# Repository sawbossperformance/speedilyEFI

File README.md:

# speedilyEFI
Arduino based projects for the Automotive Industry

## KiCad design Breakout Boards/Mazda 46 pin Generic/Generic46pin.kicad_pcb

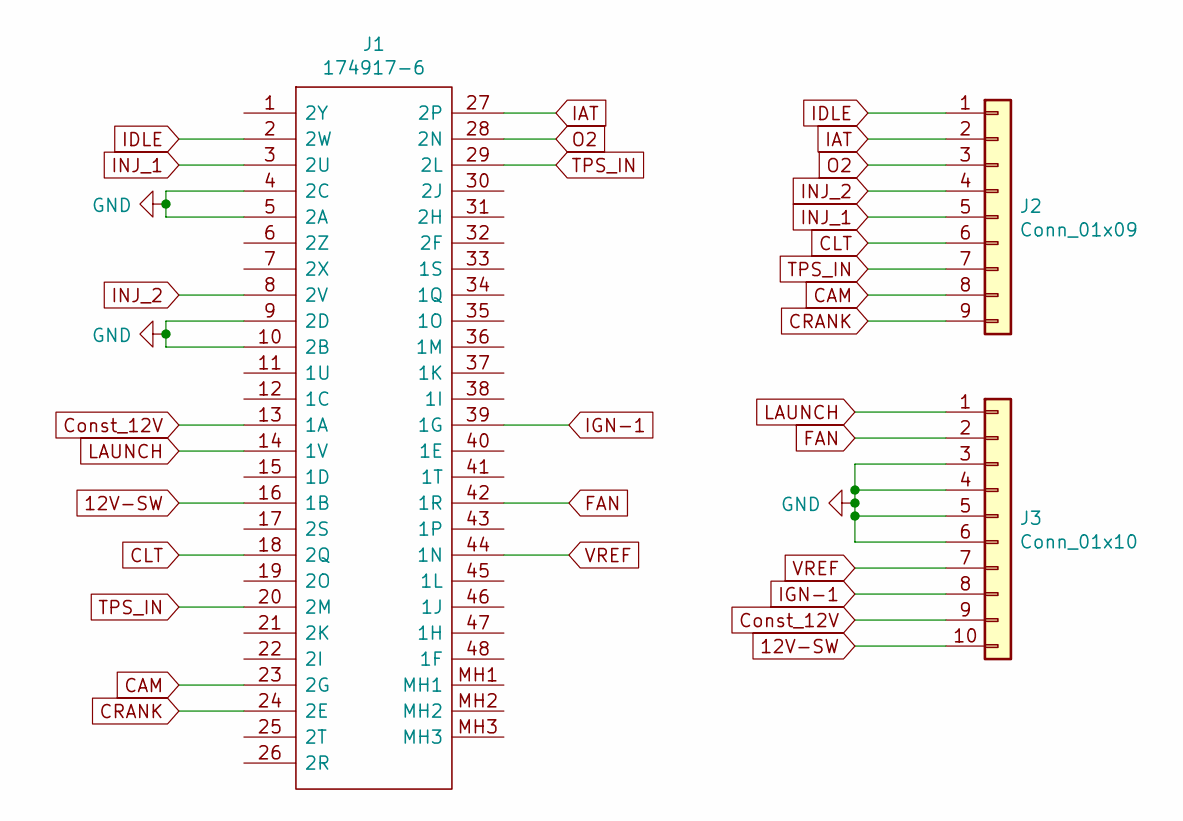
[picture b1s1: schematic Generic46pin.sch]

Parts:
J1: 174917-6; 1749176; Manufacturer_Part_Number 174917-6; Mouser Part Number 571-174917-6
J2: Conn_01x09; PinHeader_1x09_P2.54mm_Horizontal
J3: Conn_01x10; PinHeader_1x10_P2.54mm_Horizontal

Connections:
12V-SW: J1.16 (1B), J3.10
CAM: J1.23 (2G), J2.8
CLT: J1.18 (2Q), J2.6
CRANK: J1.24 (2E), J2.9
Const_12V: J1.13 (1A), J3.9
FAN: J1.42 (1R), J3.2
GND: J1.4 (2C), J1.5 (2A), J1.9 (2D), J1.10 (2B), J3.3, J3.4, J3.5, J3.6
IAT: J1.27 (2P), J2.2
IDLE: J1.2 (2W), J2.1
IGN-1: J1.39 (1G), J3.8
INJ_1: J1.3 (2U), J2.5
INJ_2: J1.8 (2V), J2.4
LAUNCH: J1.14 (1V), J3.1
O2: J1.28 (2N), J2.3
TPS_IN: J1.20 (2M), J1.29 (2L), J2.7
VREF: J1.44 (1N), J3.7

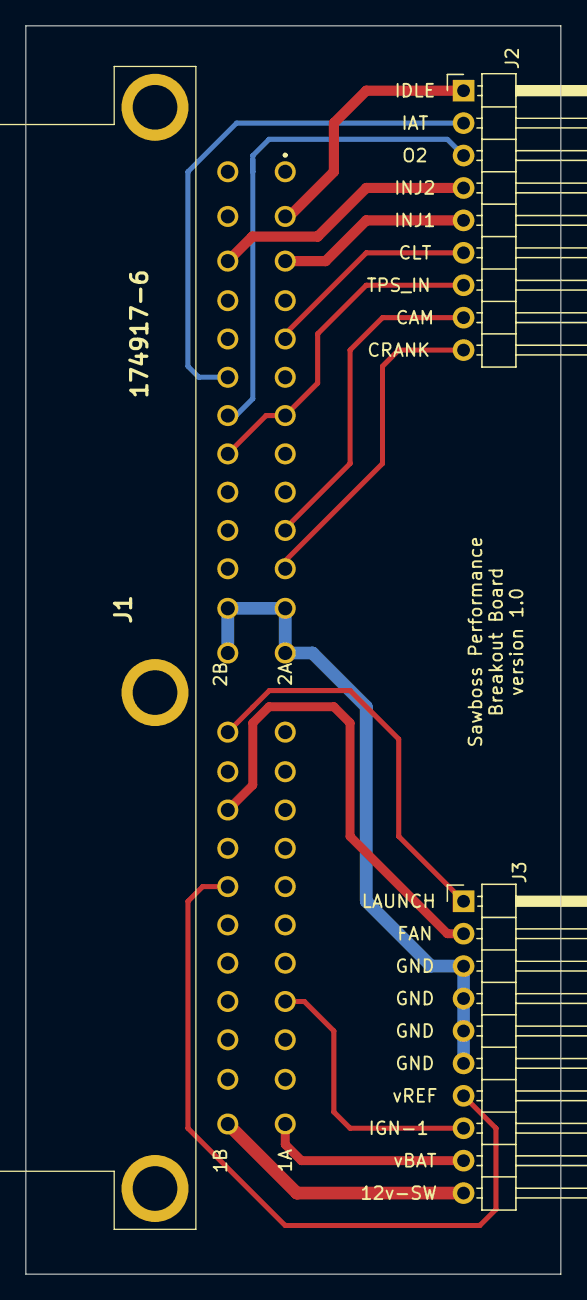
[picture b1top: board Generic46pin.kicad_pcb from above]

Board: 2 copper layers, 41.9 x 97.8 mm, 3 parts (0 on the bottom side), 16 nets.

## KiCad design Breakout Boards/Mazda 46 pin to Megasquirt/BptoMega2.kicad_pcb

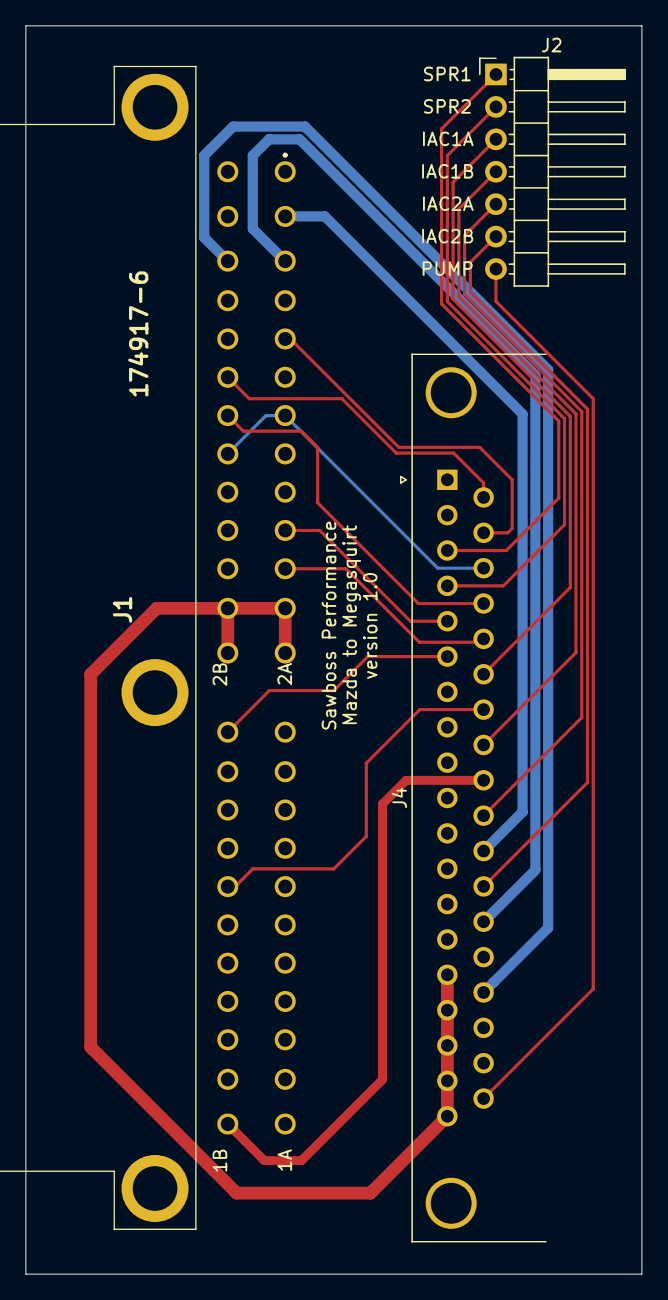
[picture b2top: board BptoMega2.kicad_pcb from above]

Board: 2 copper layers, 48.3 x 97.8 mm, 3 parts (0 on the bottom side), 20 nets.

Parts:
J1: 174917-6; 1749176
J2: Conn_01x07; PinHeader_1x07_P2.54mm_Horizontal
J4: DB37_Female; DSUB-37_Female_Horizontal_P2.77x2.84mm_EdgePinOffset4.94mm_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

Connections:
12V-SW: J1.16, J4.28
CAM: J1.23, J4.5
CLT: J1.18, J4.21
CRANK: J1.24, J4.24
GND: J1.4, J1.5, J1.9, J1.10, J4.15, J4.16, J4.17, J4.18, J4.19
IAC1A: J2.3, J4.25
IAC1B: J2.4, J4.27
IAC2A: J2.5, J4.29
IAC2B: J2.6, J4.31
IAT: J1.27, J4.20
IDLE: J1.2, J4.30
INJ_1: J1.3, J4.32
INJ_2: J1.8, J4.34
LAUNCH: J1.14, J4.6
O2: J1.28, J4.23
PUMP: J2.7, J4.37
SPR1: J2.1, J4.3
SPR2: J2.2, J4.4
TPS_IN: J1.20, J1.29, J4.22
VREF: J1.44, J4.26

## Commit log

2020-06-22 52 pin connector 172319-1
    TE 52 pin ecu connector, in all major CAD software formats.
    PN:172319-1
2021-09-22 46 Pin Connector 174917-6
    Added 2 plug 46 Pin connector for Mazda B-series (B6-BP) engines
2021-09-22 Breakout Boards Projects
    Mazda 46 pin to generic boards and Mazda 46 pin to Megasquirt
